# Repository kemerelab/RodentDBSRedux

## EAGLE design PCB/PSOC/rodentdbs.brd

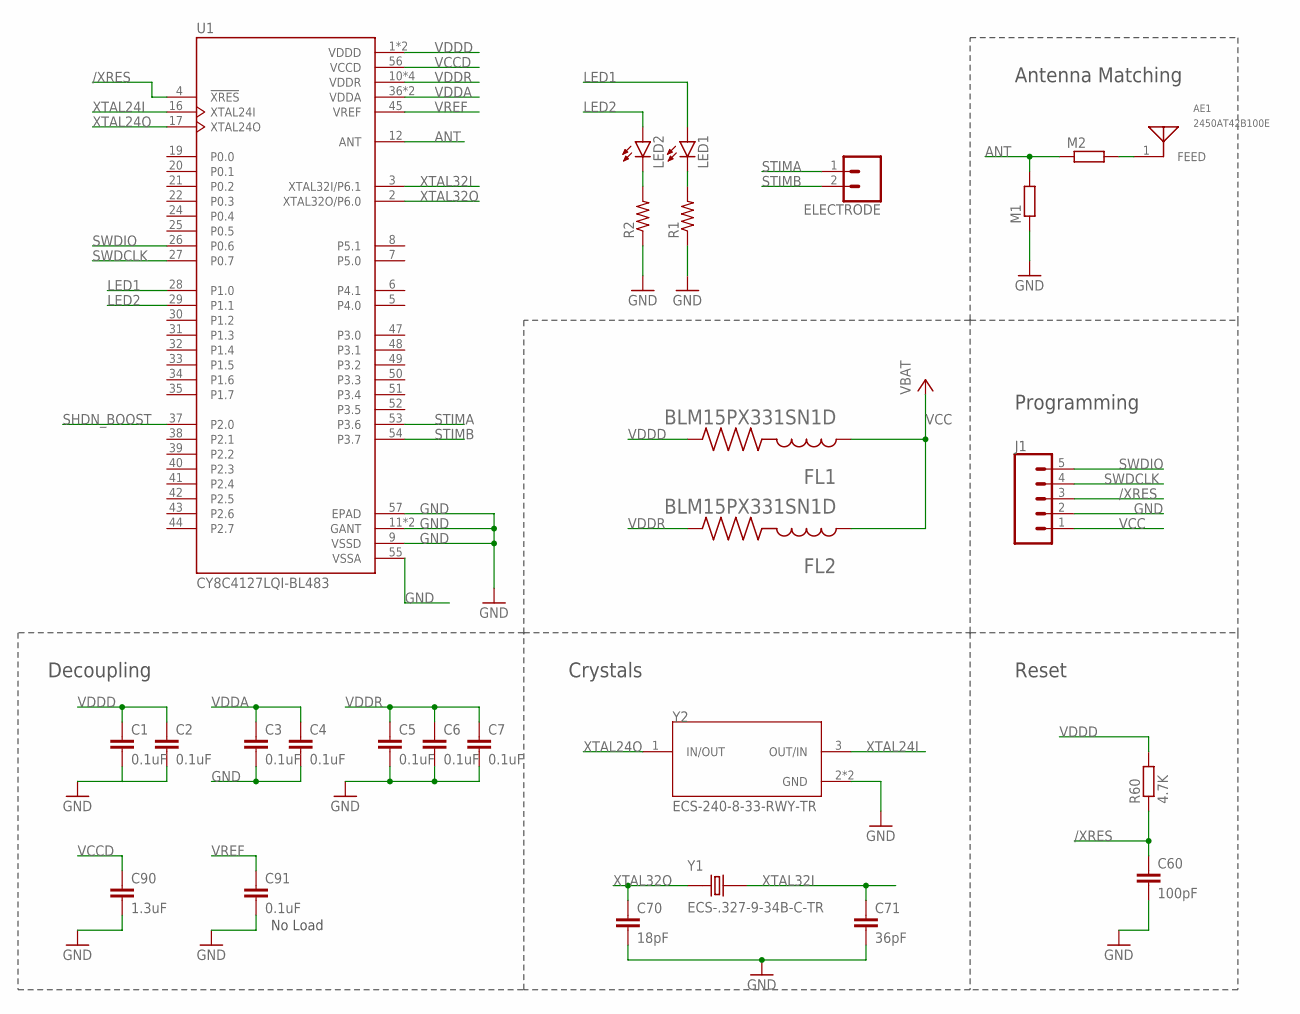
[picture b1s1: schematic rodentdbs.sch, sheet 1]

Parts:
AE1: 2450AT42B100E; XCVR_2450AT42B100E
C1, C2, C3, C4, C5, C6, C7, C91: 0.1uF; C0402
C60: 100pF; C0402
C70: 18pF; C0402
C71: 36pF; C0402
C90: 1.3uF; C0402
ELECTRODE: CONN_02; 1X02
FL1, FL2: BLM15PX331SN1D; BEADC1005X55N
J1: CONN_05LOCK; 1X05_LOCK
LED1, LED2: LEDSML0603; SML0603
M1, M2: R-EU_R0402; R0402
R1, R2: R-US_R0402; R0402
R60: 4.7K; R0402
U1: CY8C4127LQI-BL483; QFN40P700X700X60-57N
Y1: ECS-.327-9-34B-C-TR; XTAL_ECS-.327-9-34B-C-TR
Y2: ECS-240-8-33-RWY-TR; XTAL_ECS-240-8-33-RWY-TR

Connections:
/XRES: C60.1, J1.3, R60.1, U1.4 (!XRES)
ANT: M1.2, M2.1, U1.12 (ANT)
GND: C1.2, C2.2, C3.2, C4.2, C5.2, C6.2, C7.2, C60.2, C70.2, C71.2, C90.2, C91.2, J1.2, M1.1, R1.1, R2.1, U1.9 (VSSD), U1.11 (GANT), U1.13 (GANT), U1.55 (VSSA), U1.57 (EPAD), Y2.2 (GND), Y2.4 (GND); also elsewhere on the board
LED1: LED1.A, U1.28 (P1.0)
LED2: LED2.A, U1.29 (P1.1)
unnamed: LED1.C, R1.2
unnamed: AE1.1, M2.2
unnamed: LED2.C, R2.2
SHDN_BOOST: U1.37 (P2.0)
STIMA: ELECTRODE.1, U1.53 (P3.6)
STIMB: ELECTRODE.2, U1.54 (P3.7)
SWDCLK: J1.4, U1.27 (P0.7)
SWDIO: J1.5, U1.26 (P0.6)
VCC: FL1.1, FL2.1, J1.1; also elsewhere on the board
VCCD: C90.1, U1.56 (VCCD)
VDDA: C3.1, C4.1, U1.36 (VDDA), U1.46 (VDDA); also elsewhere on the board
VDDD: C1.1, C2.1, FL1.2, R60.2, U1.1 (VDDD), U1.23 (VDDD)
VDDR: C5.1, C6.1, C7.1, FL2.2, U1.10 (VDDR), U1.14 (VDDR), U1.15 (VDDR), U1.18 (VDDR)
VREF: C91.1, U1.45 (VREF)
XTAL24I: U1.16 (XTAL24I), Y2.3 (OUT/IN)
XTAL24O: U1.17 (XTAL24O), Y2.1 (IN/OUT)
XTAL32I: C71.1, U1.3 (XTAL32I/P6.1), Y1.2
XTAL32O: C70.1, U1.2 (XTAL32O/P6.0), Y1.1

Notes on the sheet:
Decoupling
Crystals
Reset
Programming
No Load
Antenna Matching

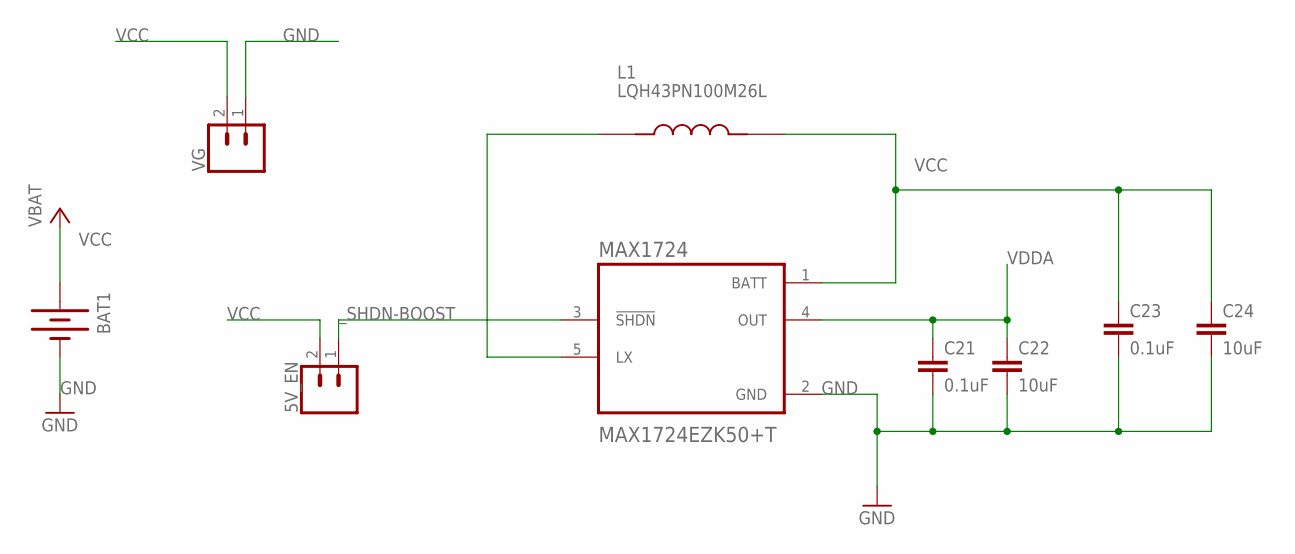
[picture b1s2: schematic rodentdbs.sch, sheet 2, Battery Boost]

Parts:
5V_EN: CONN_02; 1X02
BAT1: BATTERYBU2032SM; BU2032SM
C21, C23: 0.1uF; C0402
C22, C24: 10uF; C0603
L1: LQH43PN100M26L; IND_LQH43PN100M26L
MAX1724: MAX1724EZK50+T; SOT95P275X110-5N
VG: CONN_02; 1X02

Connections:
GND: BAT1.P$2 (-), C21.2, C22.2, C23.2, C24.2, MAX1724.2 (GND), VG.1; also elsewhere on the board
unnamed: L1.1, MAX1724.5 (LX)
VCC: 5V_EN.2, BAT1.P$1 (+), C23.1, C24.1, L1.2, MAX1724.1 (BATT), VG.2; also elsewhere on the board
VDDA: C21.1, C22.1, MAX1724.4 (OUT); also elsewhere on the board
_SHDN-BOOST: 5V_EN.1, MAX1724.3 (!SHDN)

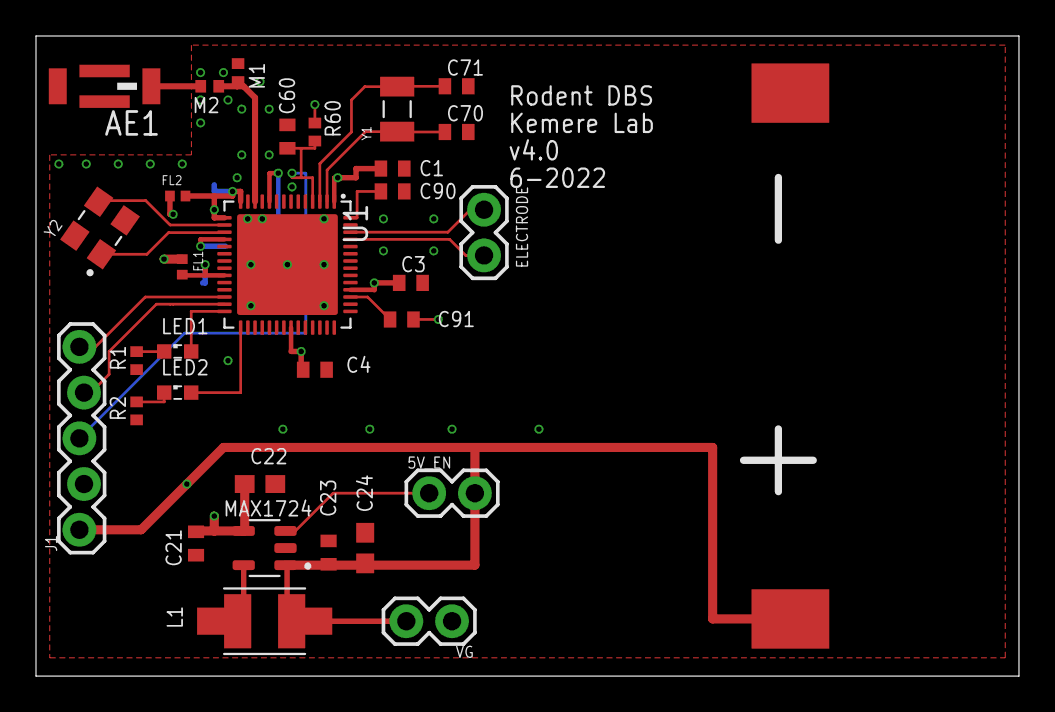
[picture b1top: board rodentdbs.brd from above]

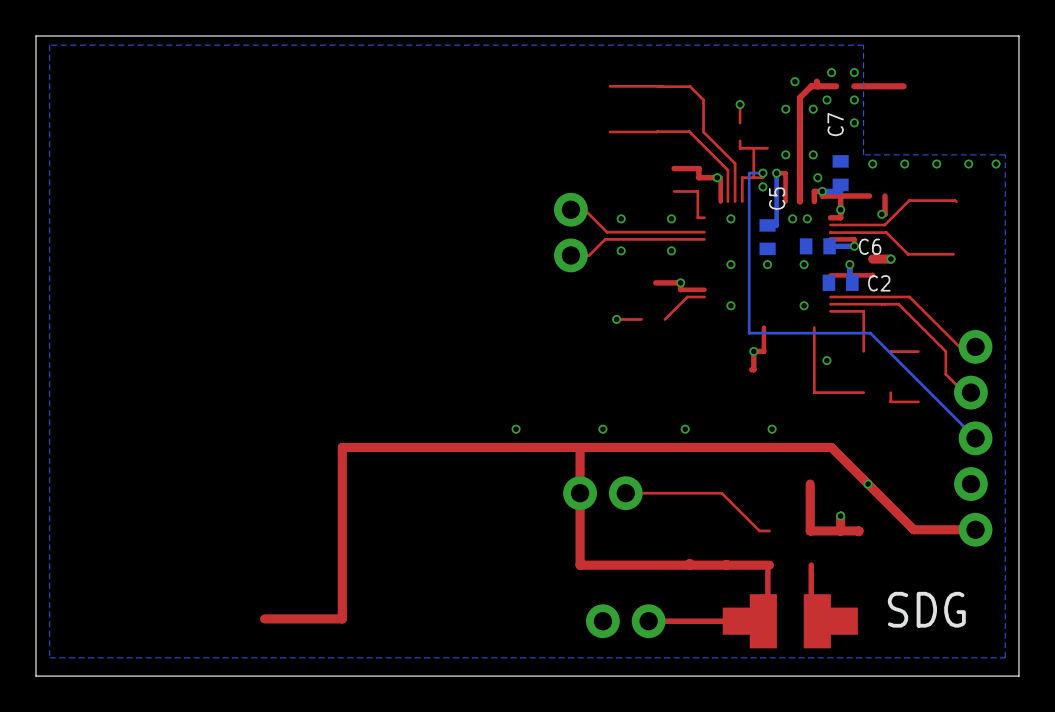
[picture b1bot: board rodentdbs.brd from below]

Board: 4 copper layers, 54.6 x 35.6 mm, 36 parts (4 on the bottom side), 24 nets.

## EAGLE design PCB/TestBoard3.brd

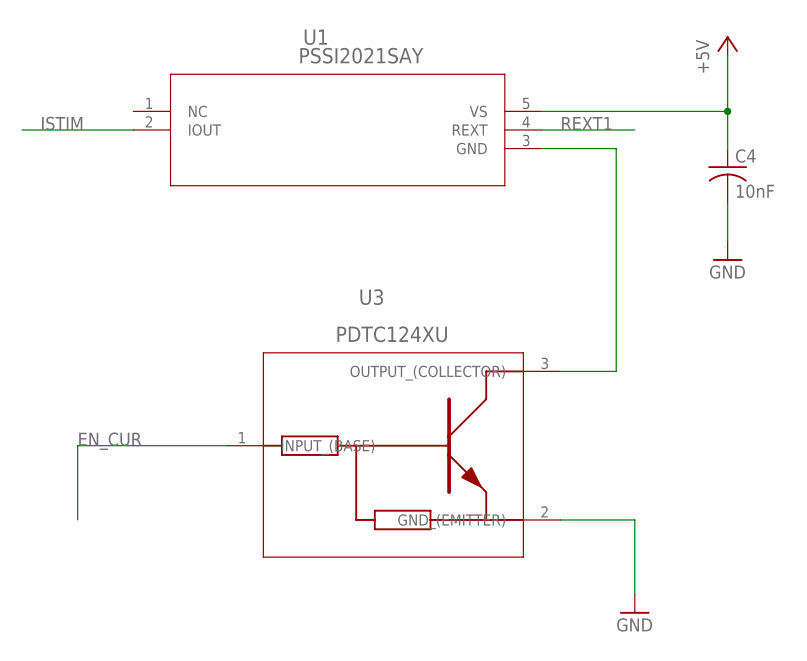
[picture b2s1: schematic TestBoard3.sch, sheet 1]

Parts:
C4: 10nF; C0603
U1: PSSI2021SAY; SOT353_NXP
U3: PDTC124XU; SOT323_NXP

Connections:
+5V: C4.1, U1.5 (VS); also elsewhere on the board
EN_CUR: U3.1 (INPUT_(BASE)); also elsewhere on the board
GND: C4.2, U3.2 (GND_(EMITTER)); also elsewhere on the board
ISTIM: U1.2 (IOUT); also elsewhere on the board
unnamed: U1.3 (GND), U3.3 (OUTPUT_(COLLECTOR))
REXT1: U1.4 (REXT); also elsewhere on the board

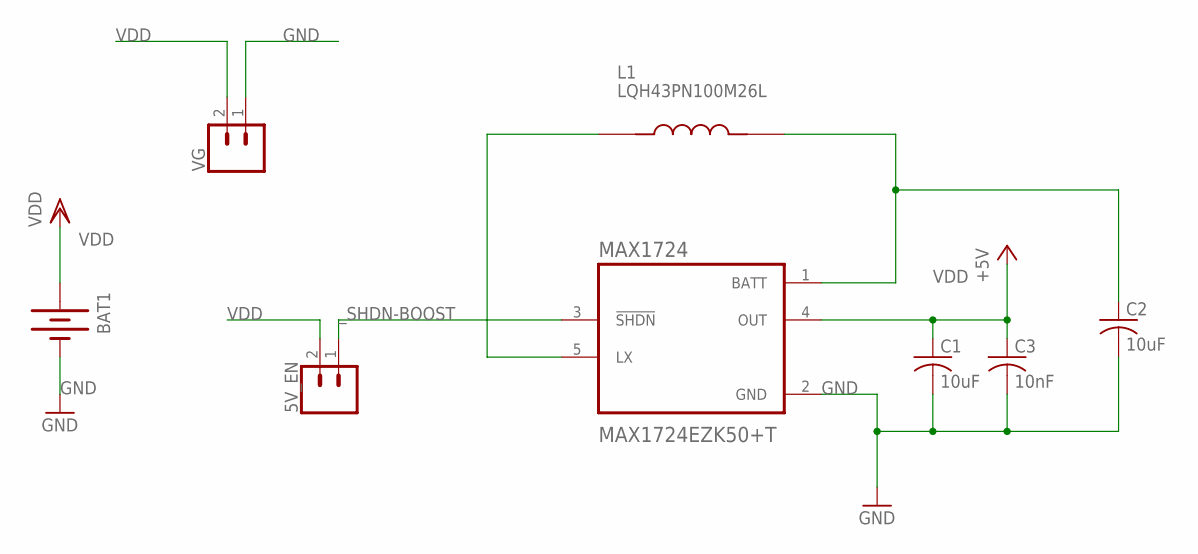
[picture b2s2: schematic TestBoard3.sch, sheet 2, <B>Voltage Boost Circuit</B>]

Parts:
5V_EN: CONN_02; 1X02
BAT1: BATTERYBU2032SM; BU2032SM
C1, C2: 10uF; C1206
C3: 10nF; C0603
L1: LQH43PN100M26L; IND_LQH43PN100M26L
MAX1724: MAX1724EZK50+T; SOT95P275X110-5N
VG: CONN_02; 1X02

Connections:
+5V: C1.1, C3.1, MAX1724.4 (OUT); also elsewhere on the board
GND: BAT1.P$2 (-), C1.2, C2.2, C3.2, MAX1724.2 (GND), VG.1; also elsewhere on the board
unnamed: L1.1, MAX1724.5 (LX)
VDD: 5V_EN.2, BAT1.P$1 (+), C2.1, L1.2, MAX1724.1 (BATT), VG.2; also elsewhere on the board
_SHDN-BOOST: 5V_EN.1, MAX1724.3 (!SHDN); also elsewhere on the board

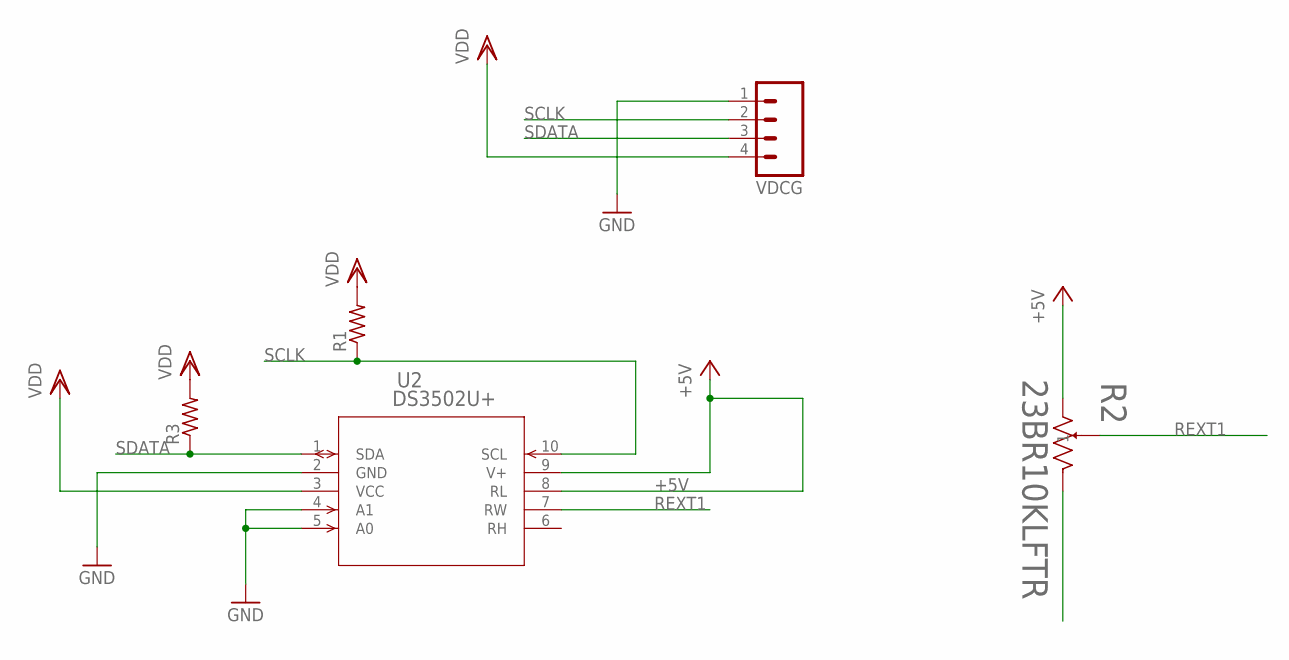
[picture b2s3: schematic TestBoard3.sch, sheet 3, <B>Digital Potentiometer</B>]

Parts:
R1, R3: R-US_R0603; R0603
R2: 23BR10KLFTR; RES3_23B_TTE
U2: DS3502U+; 21-0061_U10+2_MXM
VDCG: M04LOCK; 1X04_LOCK

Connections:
+5V: R2.1, U2.8 (RL), U2.9 (V+); also elsewhere on the board
GND: U2.2 (GND), U2.4 (A1), U2.5 (A0), VDCG.1; also elsewhere on the board
REXT1: R2.2, U2.7 (RW); also elsewhere on the board
SCLK: R1.1, U2.10 (SCL), VDCG.2; also elsewhere on the board
SDATA: R3.1, U2.1 (SDA), VDCG.3; also elsewhere on the board
VDD: R1.2, R3.2, U2.3 (VCC), VDCG.4; also elsewhere on the board

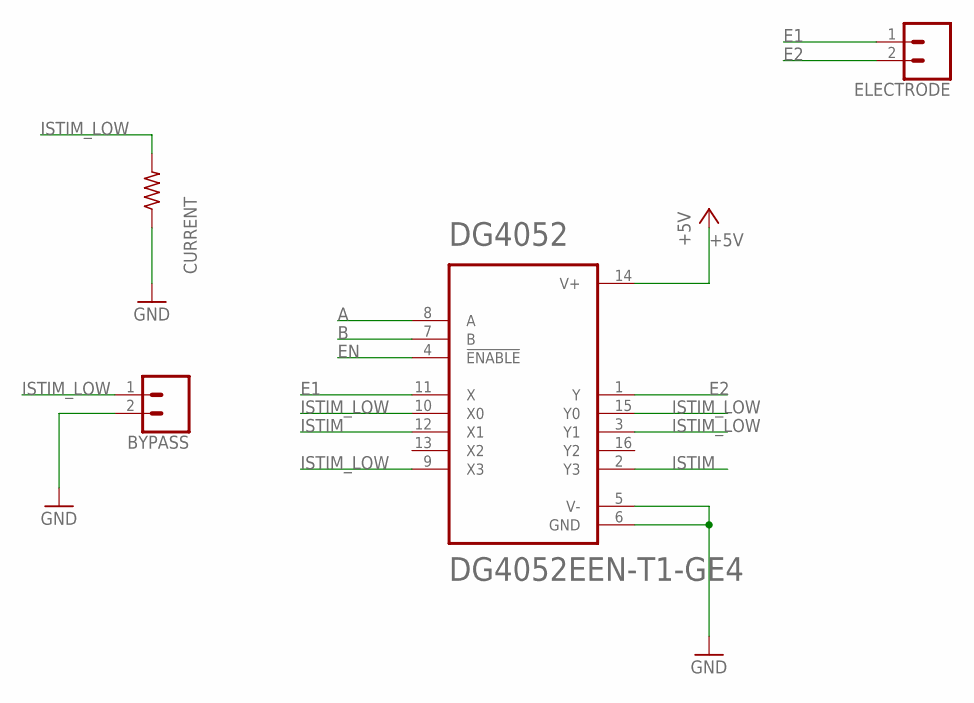
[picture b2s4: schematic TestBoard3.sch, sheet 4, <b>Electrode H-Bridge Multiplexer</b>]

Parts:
BYPASS: CONN_02LOCK; 1X02_LOCK
CURRENT: R-US_0204/7; 0204/7
DG4052: DG4052EEN-T1-GE4; QFN40P260X180X60-16N
ELECTRODE: CONN_02; 1X02

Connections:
+5V: DG4052.14 (V+); also elsewhere on the board
A: DG4052.8 (A); also elsewhere on the board
B: DG4052.7 (B); also elsewhere on the board
E1: DG4052.11 (X), ELECTRODE.1
E2: DG4052.1 (Y), ELECTRODE.2
EN: DG4052.4 (!ENABLE); also elsewhere on the board
GND: BYPASS.2, CURRENT.1, DG4052.5 (V-), DG4052.6 (GND); also elsewhere on the board
ISTIM: DG4052.2 (Y3), DG4052.12 (X1); also elsewhere on the board
ISTIM_LOW: BYPASS.1, CURRENT.2, DG4052.3 (Y1), DG4052.9 (X3), DG4052.10 (X0), DG4052.15 (Y0); also elsewhere on the board

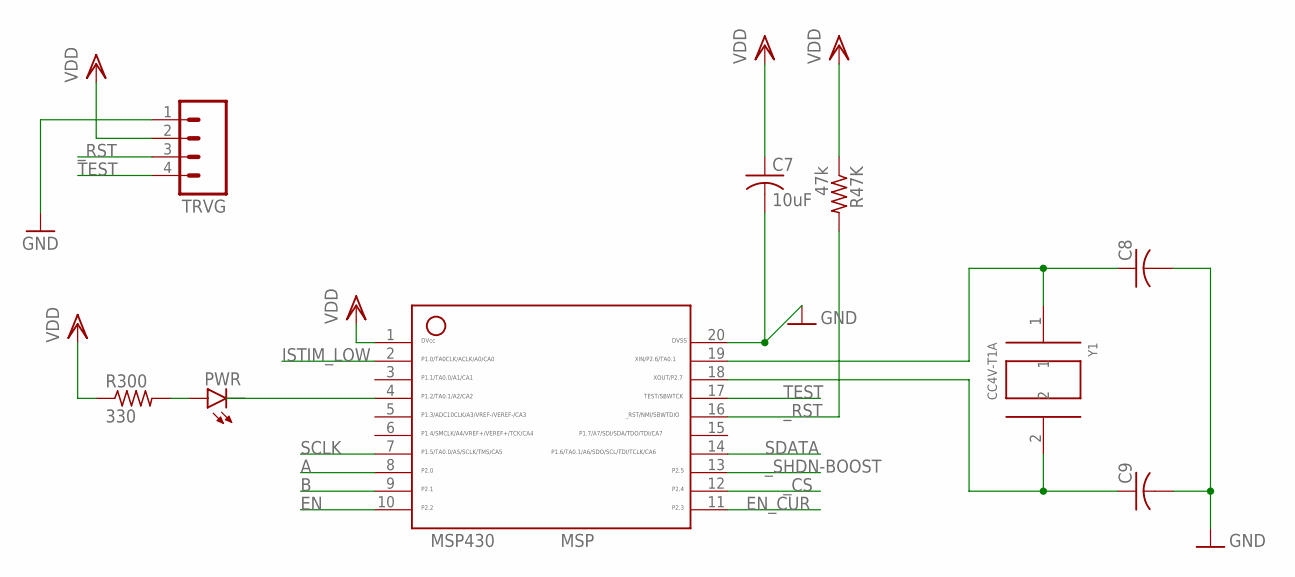
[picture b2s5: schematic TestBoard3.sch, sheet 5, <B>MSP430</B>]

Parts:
C7: 10uF; C1206
C8, C9: C-USC0603; C0603
MSP430: MSP; 20_PIN
PWR: LEDCHIPLED_0603; CHIPLED_0603
R47K: 47k; R0603
R300: 330; R0603
TRVG: M04LOCK; 1X04_LOCK
Y1: CC4V-T1A

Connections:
A: MSP430.8; also elsewhere on the board
B: MSP430.9; also elsewhere on the board
EN: MSP430.10; also elsewhere on the board
EN_CUR: MSP430.11; also elsewhere on the board
GND: C7.2, C8.2, C9.2, MSP430.20, TRVG.1; also elsewhere on the board
ISTIM_LOW: MSP430.2; also elsewhere on the board
unnamed: MSP430.4, PWR.C
unnamed: PWR.A, R300.2
unnamed: C8.1, MSP430.19, Y1.1
unnamed: C9.1, MSP430.18, Y1.2
SCLK: MSP430.7; also elsewhere on the board
SDATA: MSP430.14; also elsewhere on the board
TEST: MSP430.17, TRVG.4
VDD: C7.1, MSP430.1, R47K.1, R300.1, TRVG.2; also elsewhere on the board
_CS: MSP430.12
_RST: MSP430.16, R47K.2, TRVG.3
_SHDN-BOOST: MSP430.13; also elsewhere on the board

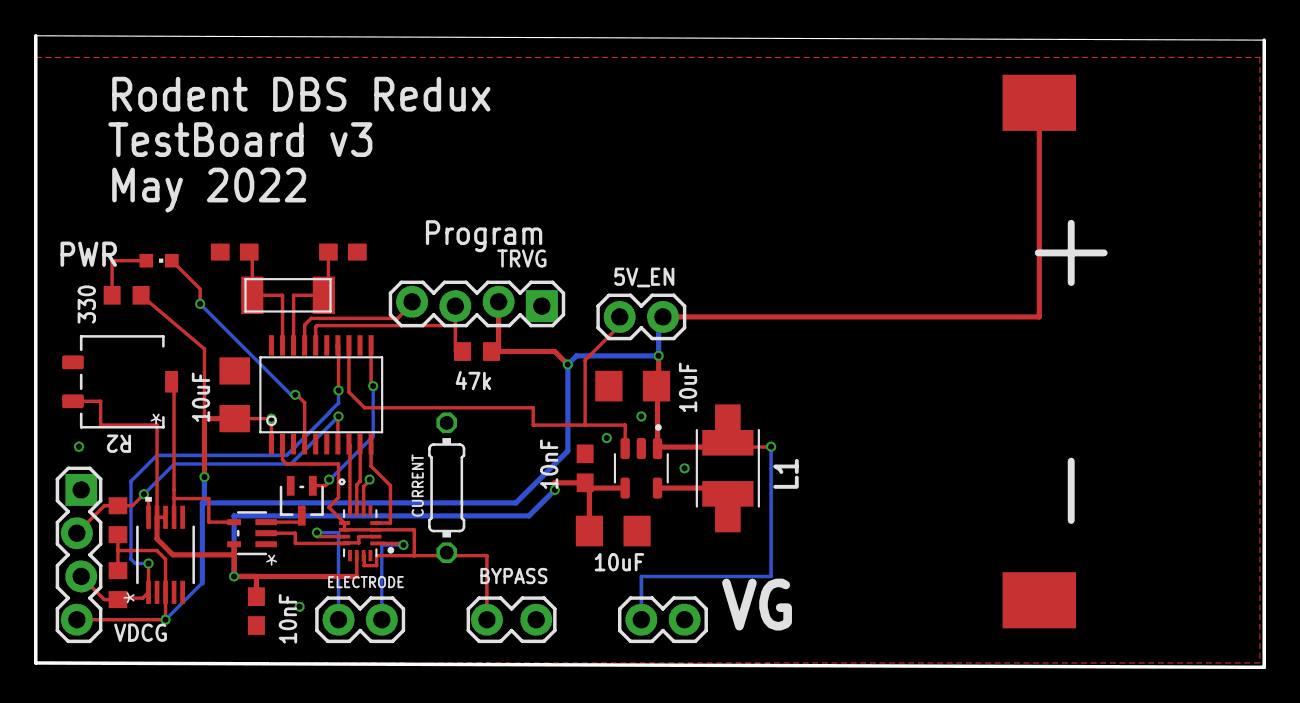
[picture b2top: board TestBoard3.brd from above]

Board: 2 copper layers, 72.1 x 37.1 mm, 29 parts (0 on the bottom side), 23 nets.

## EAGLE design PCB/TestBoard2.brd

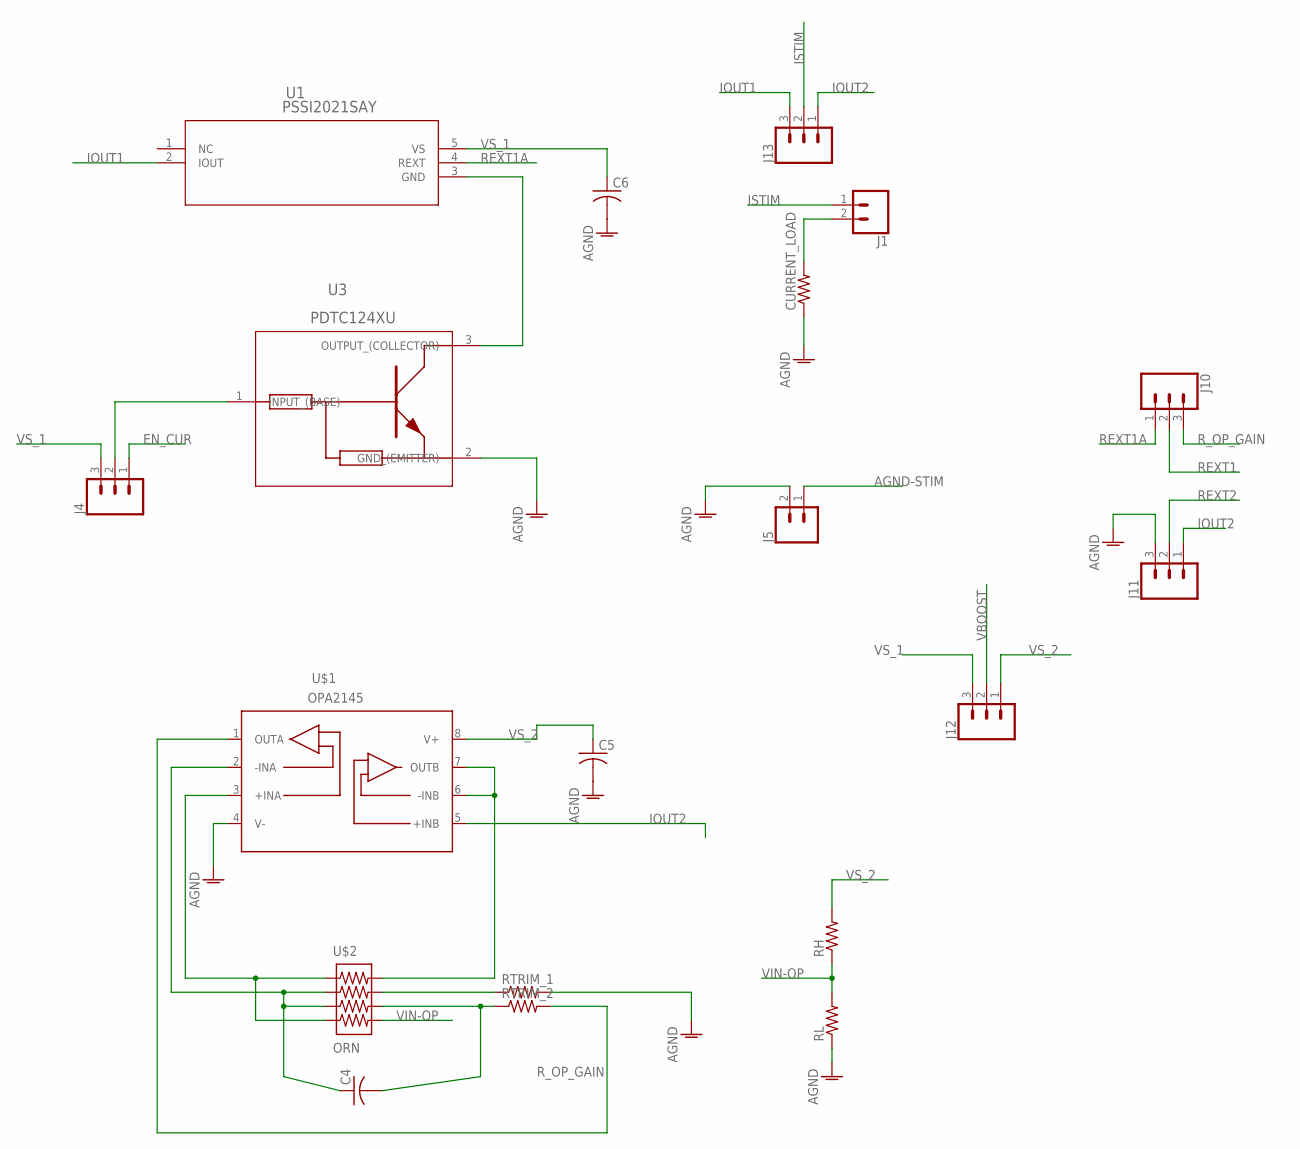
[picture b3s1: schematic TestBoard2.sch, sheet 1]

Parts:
C4, C5, C6: C-USC0603; C0603
CURRENT_LOAD: R-US_0204/7; 0204/7
J1: CONN_02LOCK; 1X02_LOCK
J4, J12, J13: CONN_03LOCK; 1X03_LOCK
J5: CONN_02; 1X02
J10, J11: CONN_03; 1X03
RH: R-US_R0603; R0603
RL: R-US_R0603; R0603
RTRIM_1, RTRIM_2: R-US_R0603; R0603
U1: PSSI2021SAY; SOT353_NXP
U3: PDTC124XU; SOT323_NXP
U$1: OPA2145; 8-VSSOP
U$2: ORN; 8-TSSOP

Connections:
AGND: C5.2, C6.2, CURRENT_LOAD.1, J5.2, J11.3, RL.1, RTRIM_1.2, U3.2 (GND_(EMITTER)), U$1.4 (V-); also elsewhere on the board
AGND-STIM: J5.1; also elsewhere on the board
EN_CUR: J4.1; also elsewhere on the board
IOUT1: J13.3, U1.2 (IOUT)
IOUT2: J11.1, J13.1, U$1.5 (+INB)
ISTIM: J1.1, J13.2; also elsewhere on the board
unnamed: J4.2, U3.1 (INPUT_(BASE))
unnamed: CURRENT_LOAD.2, J1.2
unnamed: C4.1, U$1.2 (-INA), U$2.2, U$2.3
unnamed: U1.3 (GND), U3.3 (OUTPUT_(COLLECTOR))
unnamed: U$1.3 (+INA), U$2.1, U$2.4
unnamed: U$1.6 (-INB), U$1.7 (OUTB), U$2.8
unnamed: RTRIM_1.1, U$2.7
unnamed: C4.2, RTRIM_2.1, U$2.6
REXT1: J10.2; also elsewhere on the board
REXT1A: J10.1, U1.4 (REXT)
REXT2: J11.2; also elsewhere on the board
R_OP_GAIN: J10.3, RTRIM_2.2, U$1.1 (OUTA)
VBOOST: J12.2; also elsewhere on the board
VIN-OP: RH.1, RL.2, U$2.5
VS_1: C6.1, J4.3, J12.3, U1.5 (VS)
VS_2: C5.1, J12.1, RH.2, U$1.8 (V+)

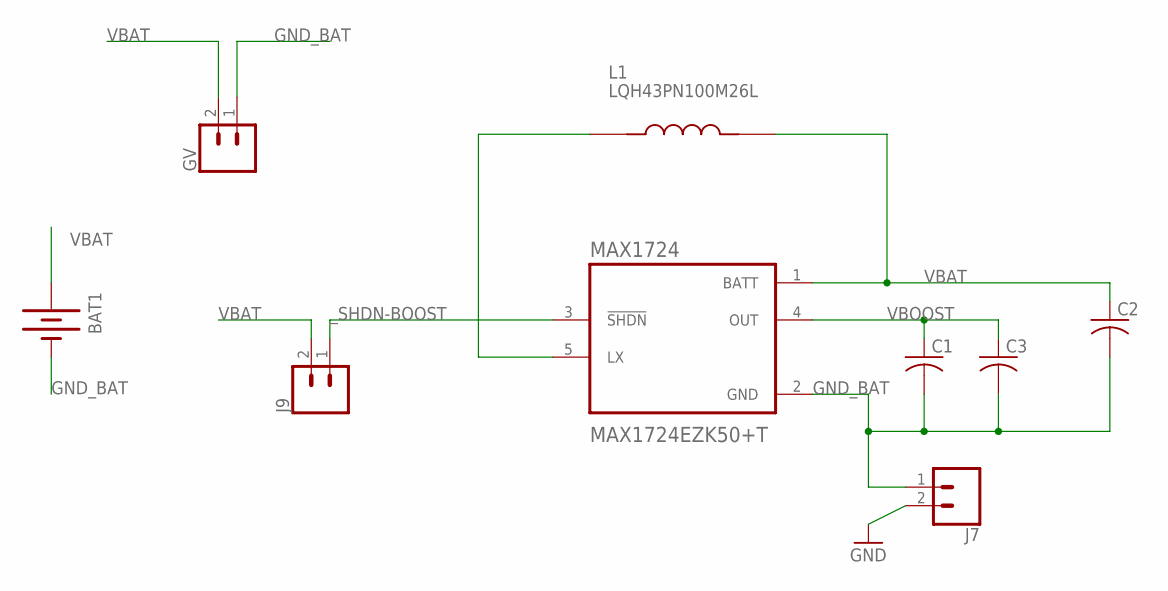
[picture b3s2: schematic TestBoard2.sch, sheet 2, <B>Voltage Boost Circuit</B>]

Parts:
BAT1: BATTERYBU2032SM; BU2032SM
C1, C2: C-USC1206; C1206
C3: C-USC0603; C0603
GV: CONN_02; 1X02
J7, J9: CONN_02; 1X02
L1: LQH43PN100M26L; IND_LQH43PN100M26L
MAX1724: MAX1724EZK50+T; SOT95P275X110-5N

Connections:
GND: J7.2; also elsewhere on the board
GND_BAT: BAT1.P$2 (-), C1.2, C2.2, C3.2, GV.1, J7.1, MAX1724.2 (GND)
unnamed: L1.1, MAX1724.5 (LX)
VBAT: BAT1.P$1 (+), C2.1, GV.2, J9.2, L1.2, MAX1724.1 (BATT); also elsewhere on the board
VBOOST: C1.1, C3.1, MAX1724.4 (OUT); also elsewhere on the board
_SHDN-BOOST: J9.1, MAX1724.3 (!SHDN); also elsewhere on the board

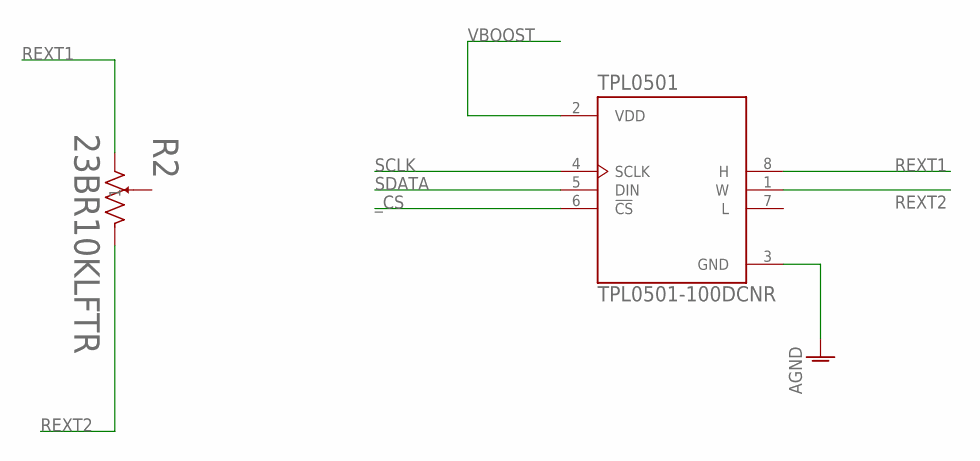
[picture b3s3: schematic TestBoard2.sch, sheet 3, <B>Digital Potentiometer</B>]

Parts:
R2: 23BR10KLFTR; RES3_23B_TTE
TPL0501: TPL0501-100DCNR; SOT65P280X145-8N

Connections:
AGND: TPL0501.3 (GND); also elsewhere on the board
REXT1: R2.1, TPL0501.8 (H); also elsewhere on the board
REXT2: R2.3, TPL0501.1 (W); also elsewhere on the board
SCLK: TPL0501.4 (SCLK); also elsewhere on the board
SDATA: TPL0501.5 (DIN); also elsewhere on the board
VBOOST: TPL0501.2 (VDD); also elsewhere on the board
_CS: TPL0501.6 (!CS!); also elsewhere on the board

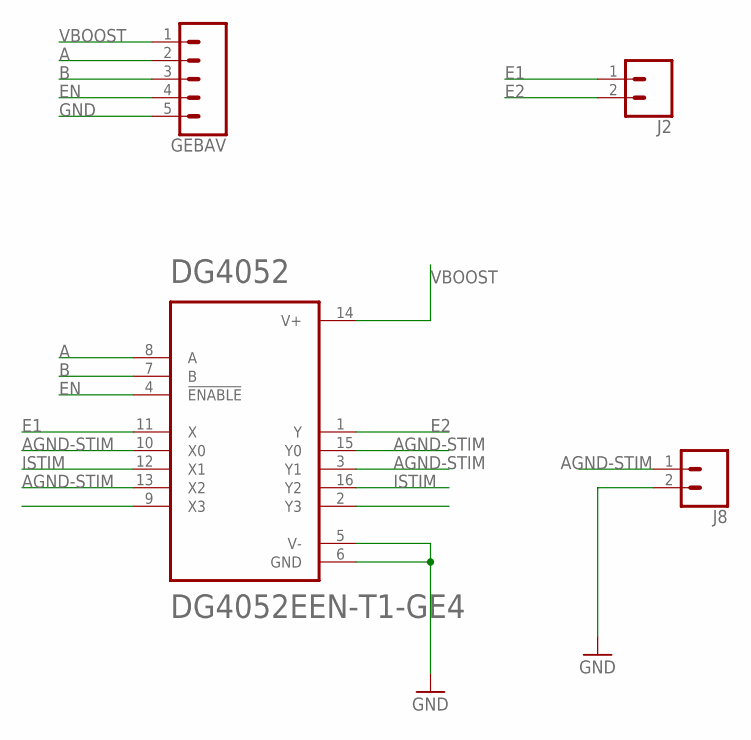
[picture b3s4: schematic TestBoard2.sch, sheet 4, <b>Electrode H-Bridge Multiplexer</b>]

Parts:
DG4052: DG4052EEN-T1-GE4; QFN40P260X180X60-16N
GEBAV: CONN_05LOCK; 1X05_LOCK
J2, J8: CONN_02; 1X02

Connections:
A: DG4052.8 (A), GEBAV.2; also elsewhere on the board
AGND-STIM: DG4052.3 (Y1), DG4052.10 (X0), DG4052.13 (X2), DG4052.15 (Y0), J8.1; also elsewhere on the board
B: DG4052.7 (B), GEBAV.3; also elsewhere on the board
E1: DG4052.11 (X), J2.1
E2: DG4052.1 (Y), J2.2
EN: DG4052.4 (!ENABLE), GEBAV.4; also elsewhere on the board
GND: DG4052.5 (V-), DG4052.6 (GND), GEBAV.5, J8.2; also elsewhere on the board
ISTIM: DG4052.12 (X1), DG4052.16 (Y2); also elsewhere on the board
VBOOST: DG4052.14 (V+), GEBAV.1; also elsewhere on the board

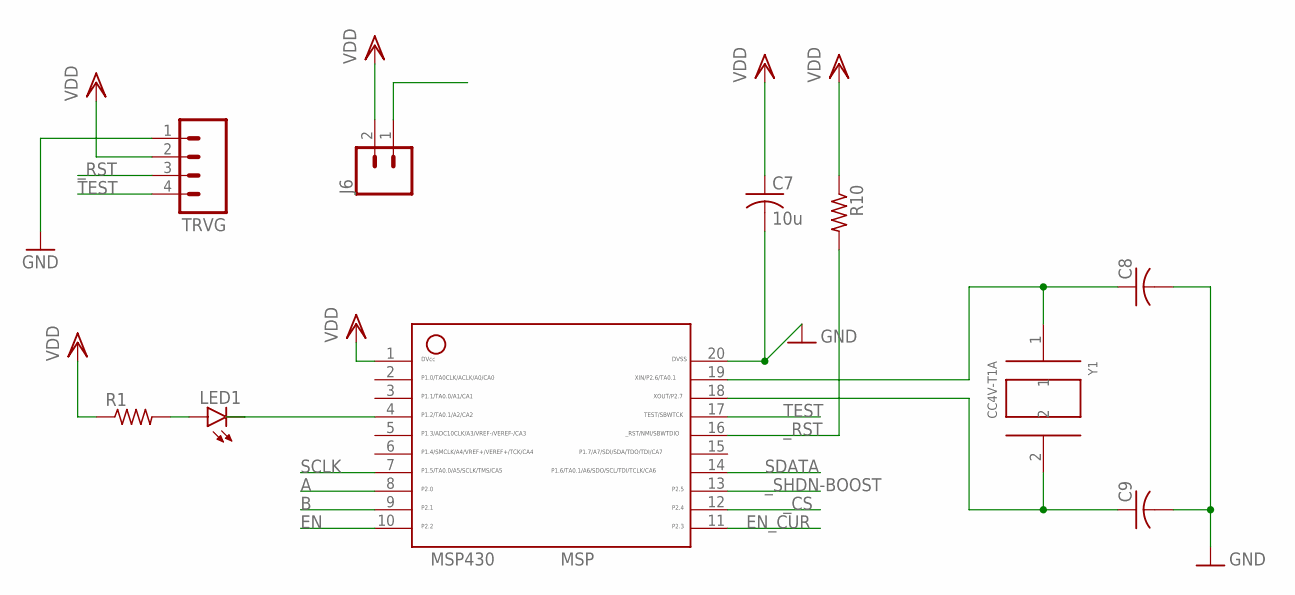
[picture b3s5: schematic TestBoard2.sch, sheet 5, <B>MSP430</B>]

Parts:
C7: 10u; C1206
C8, C9: C-USC0603; C0603
J6: CONN_02; 1X02
LED1: LEDCHIPLED_0603; CHIPLED_0603
MSP430: MSP; 20_PIN
R1, R10: R-US_R1206; R1206
TRVG: M04LOCK; 1X04_LOCK
Y1: CC4V-T1A

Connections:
A: MSP430.8; also elsewhere on the board
B: MSP430.9; also elsewhere on the board
EN: MSP430.10; also elsewhere on the board
EN_CUR: MSP430.11; also elsewhere on the board
GND: C7.2, C8.2, C9.2, MSP430.20, TRVG.1; also elsewhere on the board
unnamed: LED1.C, MSP430.4
unnamed: LED1.A, R1.2
unnamed: C8.1, MSP430.19, Y1.1
unnamed: C9.1, MSP430.18, Y1.2
SCLK: MSP430.7; also elsewhere on the board
SDATA: MSP430.14; also elsewhere on the board
TEST: MSP430.17, TRVG.4
VBAT: J6.1; also elsewhere on the board
VDD: C7.1, J6.2, MSP430.1, R1.1, R10.1, TRVG.2
_CS: MSP430.12; also elsewhere on the board
_RST: MSP430.16, R10.2, TRVG.3
_SHDN-BOOST: MSP430.13; also elsewhere on the board

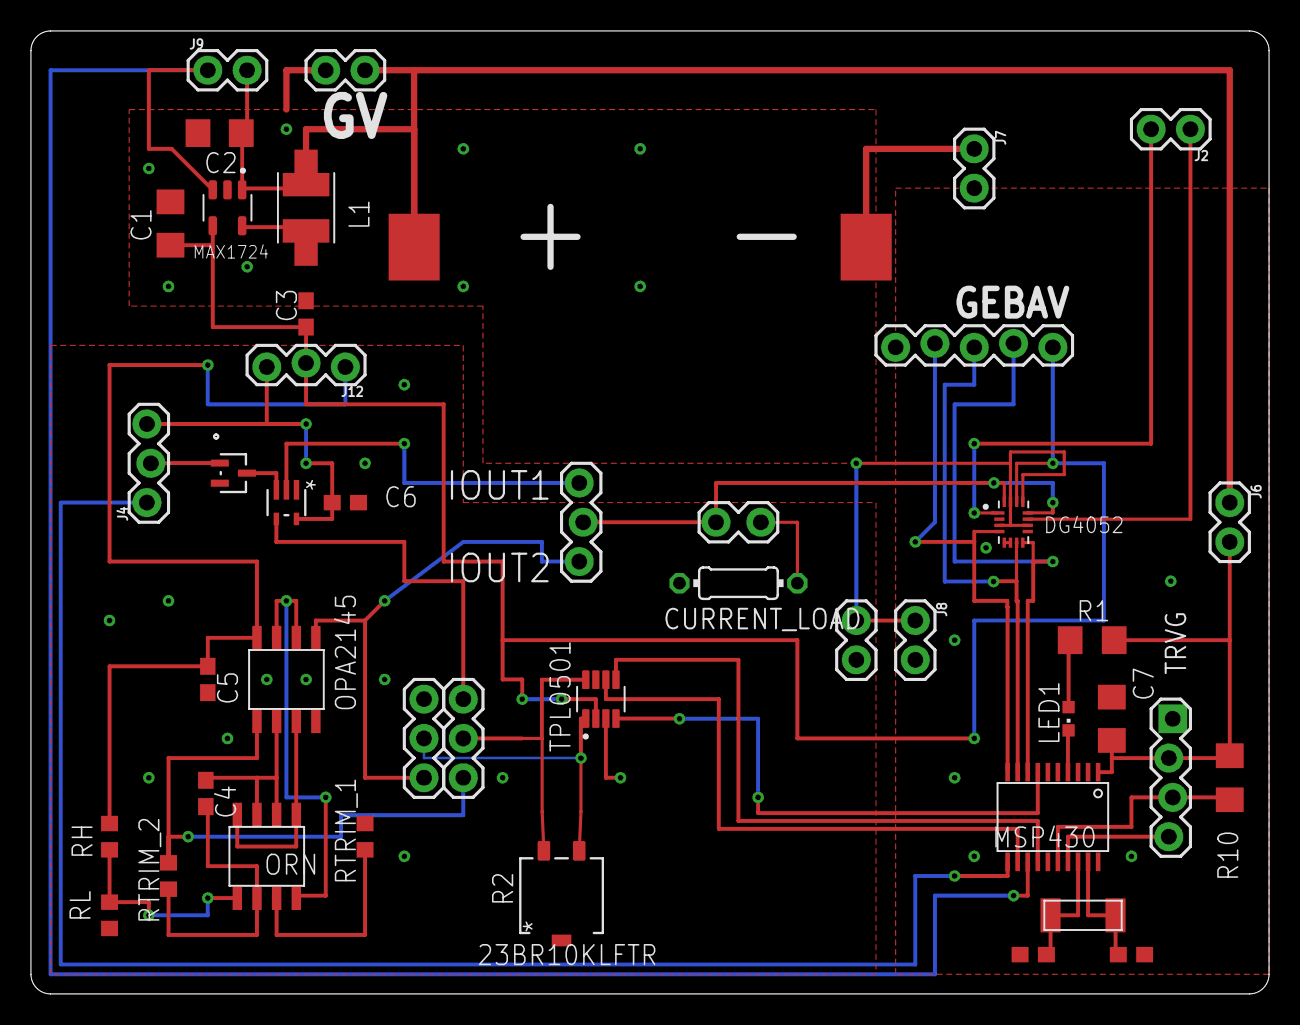
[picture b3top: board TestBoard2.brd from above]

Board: 2 copper layers, 80.0 x 62.2 mm, 44 parts (0 on the bottom side), 42 nets.

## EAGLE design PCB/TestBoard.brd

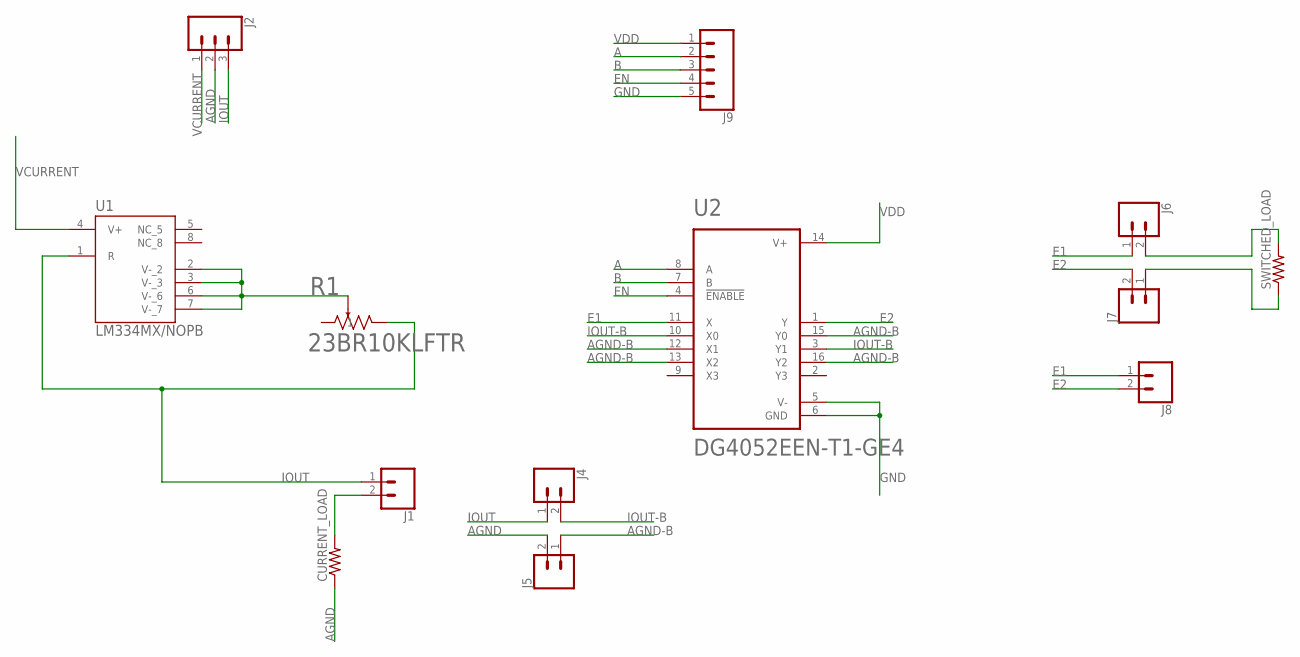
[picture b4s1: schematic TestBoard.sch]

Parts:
CURRENT_LOAD: R-US_V234/12; V234/12
J1: CONN_02LOCK; 1X02_LOCK
J2: CONN_03LOCK; 1X03_LOCK
J4, J5, J6, J7, J8: CONN_02; 1X02
J9: CONN_05LOCK; 1X05_LOCK
R1: 23BR10KLFTR; RES3_23B_TTE
SWITCHED_LOAD: R-US_V234/12; V234/12
U1: LM334MX/NOPB; SOIC127P599X175-8N
U2: DG4052EEN-T1-GE4; QFN40P260X180X60-16N

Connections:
A: J9.2, U2.8 (A)
AGND: CURRENT_LOAD.1, J2.2, J5.2
AGND-B: J5.1, U2.12 (X1), U2.13 (X2), U2.15 (Y0), U2.16 (Y2)
B: J9.3, U2.7 (B)
E1: J6.1, J8.1, U2.11 (X)
E2: J7.2, J8.2, U2.1 (Y)
EN: J9.4, U2.4 (!ENABLE)
GND: J9.5, U2.5 (V-), U2.6 (GND)
IOUT: J1.1, J2.3, J4.1, R1.3, U1.1 (R)
IOUT-B: J4.2, U2.3 (Y1), U2.10 (X0)
unnamed: J6.2, SWITCHED_LOAD.2
unnamed: R1.2, U1.2 (V-_2), U1.3 (V-_3), U1.6 (V-_6), U1.7 (V-_7)
unnamed: CURRENT_LOAD.2, J1.2
unnamed: J7.1, SWITCHED_LOAD.1
VCURRENT: J2.1, U1.4 (V+)
VDD: J9.1, U2.14 (V+)

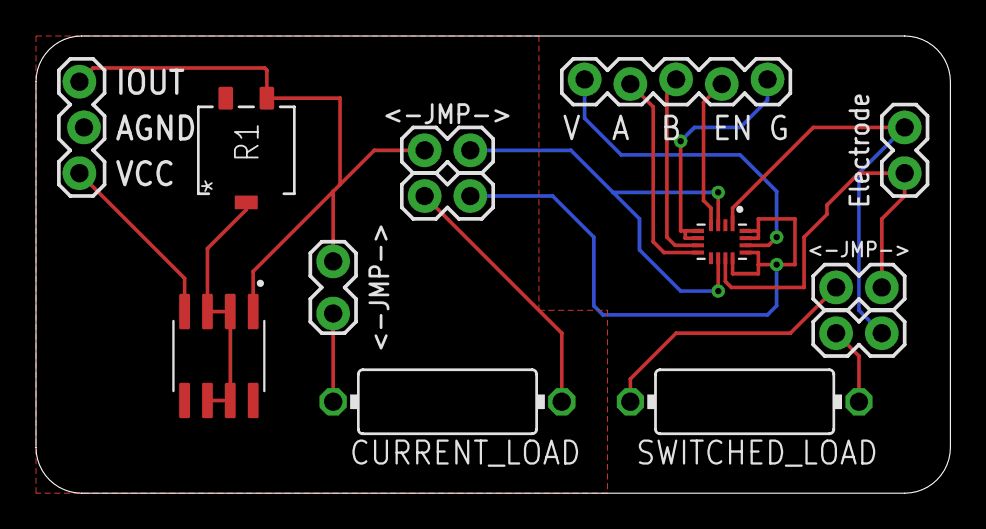
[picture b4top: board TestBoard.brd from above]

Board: 2 copper layers, 50.8 x 25.4 mm, 13 parts (0 on the bottom side), 16 nets.

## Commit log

2021-04-15 Initial commit of test board for current source and multiplexer.
2021-04-15 Added a README
2021-08-04 Updated test board
2021-09-09 Added firmware for TestBoard v2
2021-09-09 Added some data sheets
2022-05-02 Version 3 of PCB. Beginning to look at tight layout options!
2022-05-02 Version 3 of PCB. OshPark manufactured version.
2022-06-30 PSOC4 board initial

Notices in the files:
parts and their libraries:
SparkFun-Connectors: Licensing: Creative Commons ShareAlike 4.0 International - https://creativecommons.org/licenses/by-sa/4.0
COPYRIGHT: Copyright (C) 2016 Accelerated Designs. All rights reserved
COPYRIGHT: Copyright (C) 2021 Ultra Librarian. All rights reserved.
